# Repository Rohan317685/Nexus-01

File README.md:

<h1 align="center">
  <br>
  </a>
  <br>
  Nexus 01
  <br>
</h1>

<h4 align="center">
A Raspberry Pi Pico-sized devboard!

<div align="center">

</div>

<p align="center">
  <a href="#key-features">Key Features</a> •
  <a href="#pcb">PCB</a> •
  <a href="#credits">Credits</a> •
  <a href="#license">License</a>
</p>

## Key Features

- **Raspberry Pi RP2040 chip** pico like devboard
- **Multiple LED** for visual feedback
- **USB-C**
- **2-layer PCB** designed for cheap prices at bulk
- **Panelized design** for cost-effective manufacturing
- **Multiple buttons** for reset, boot and extra inbuilt button

## PCB

Designed in KiCad with help of the hackclub blueprint guide and a few more features added!

### Schematic

### PCB Layers

The 2-layer stackup:

**Layer 1 (Main routing layer):**

**Layer 2 (Mainly GPIO pins):**

**Front:**

**Back:**

### JLCPCB Order and LCSC Order

| Item | Description | Part Number | LCSC Code | Qty |
| :--- | :--- | :--- | :--- | :--- |
| **Tactile Switch** | SPST SMD 3.9x2.9mm | ALPS SKRKAHE020 | [C202388](https://www.lcsc.com/product-detail/C202388.html?s_z=n_q_C202388) | 10 || **3-Pin Header** | 1x3P 2.54mm Pitch TH | HX PZ2.54-1x3P ZZ | [C32713269](https://www.lcsc.com/product-detail/C32713269.html) | 5 |
| **3-Pin Header** | 1x3P 2.54mm Pitch TH | HX PZ2.54-1x3P ZZ | [C32713269](https://www.lcsc.com/product-detail/C32713269.html?s_z=n_q_C32713269) | 5 |
| **20-Pin Header** | 1x20P 2.54mm Pitch TH | PH2.54-1X20P-H25 | [C42431804](https://www.lcsc.com/product-detail/C42431804.html?s_z=n_q_C42431804) | 5 |

 (Had to get 5 because only multiples of 5 were allowed also got 10 buttons because I want to practice smd hand soldering and I will messup)
 Im buying from LCSC mainly because no companies atleast reliable companies sell those types of exact switches and those headers (I looked at aliexpress, digikey, mouser , rapid electronics and a few more and I decided this has the best price and very good shipping rates!)

### Order costs
- **Parts Total:** $2.25
- **Shipping:** $5.85
- **Handling Fee:** $3.00
- **PCBA:** $39.63
- **PCBA shipping:** $1.50
- **Overall Total:** **$52.23**
## Credits

This project uses:

- [KiCad](https://www.kicad.org/)
- [Onshape](https://www.onshape.com/) for 3D renders
- [Hack Club Macondo go join!!!](https://macondo.hackclub.com/projects/8)

## License

MIT

---

> Readme inspired by [@NotARoomba](https://github.com/NotARoomba) &nbsp;&middot;&nbsp; go follow him now!!! : D

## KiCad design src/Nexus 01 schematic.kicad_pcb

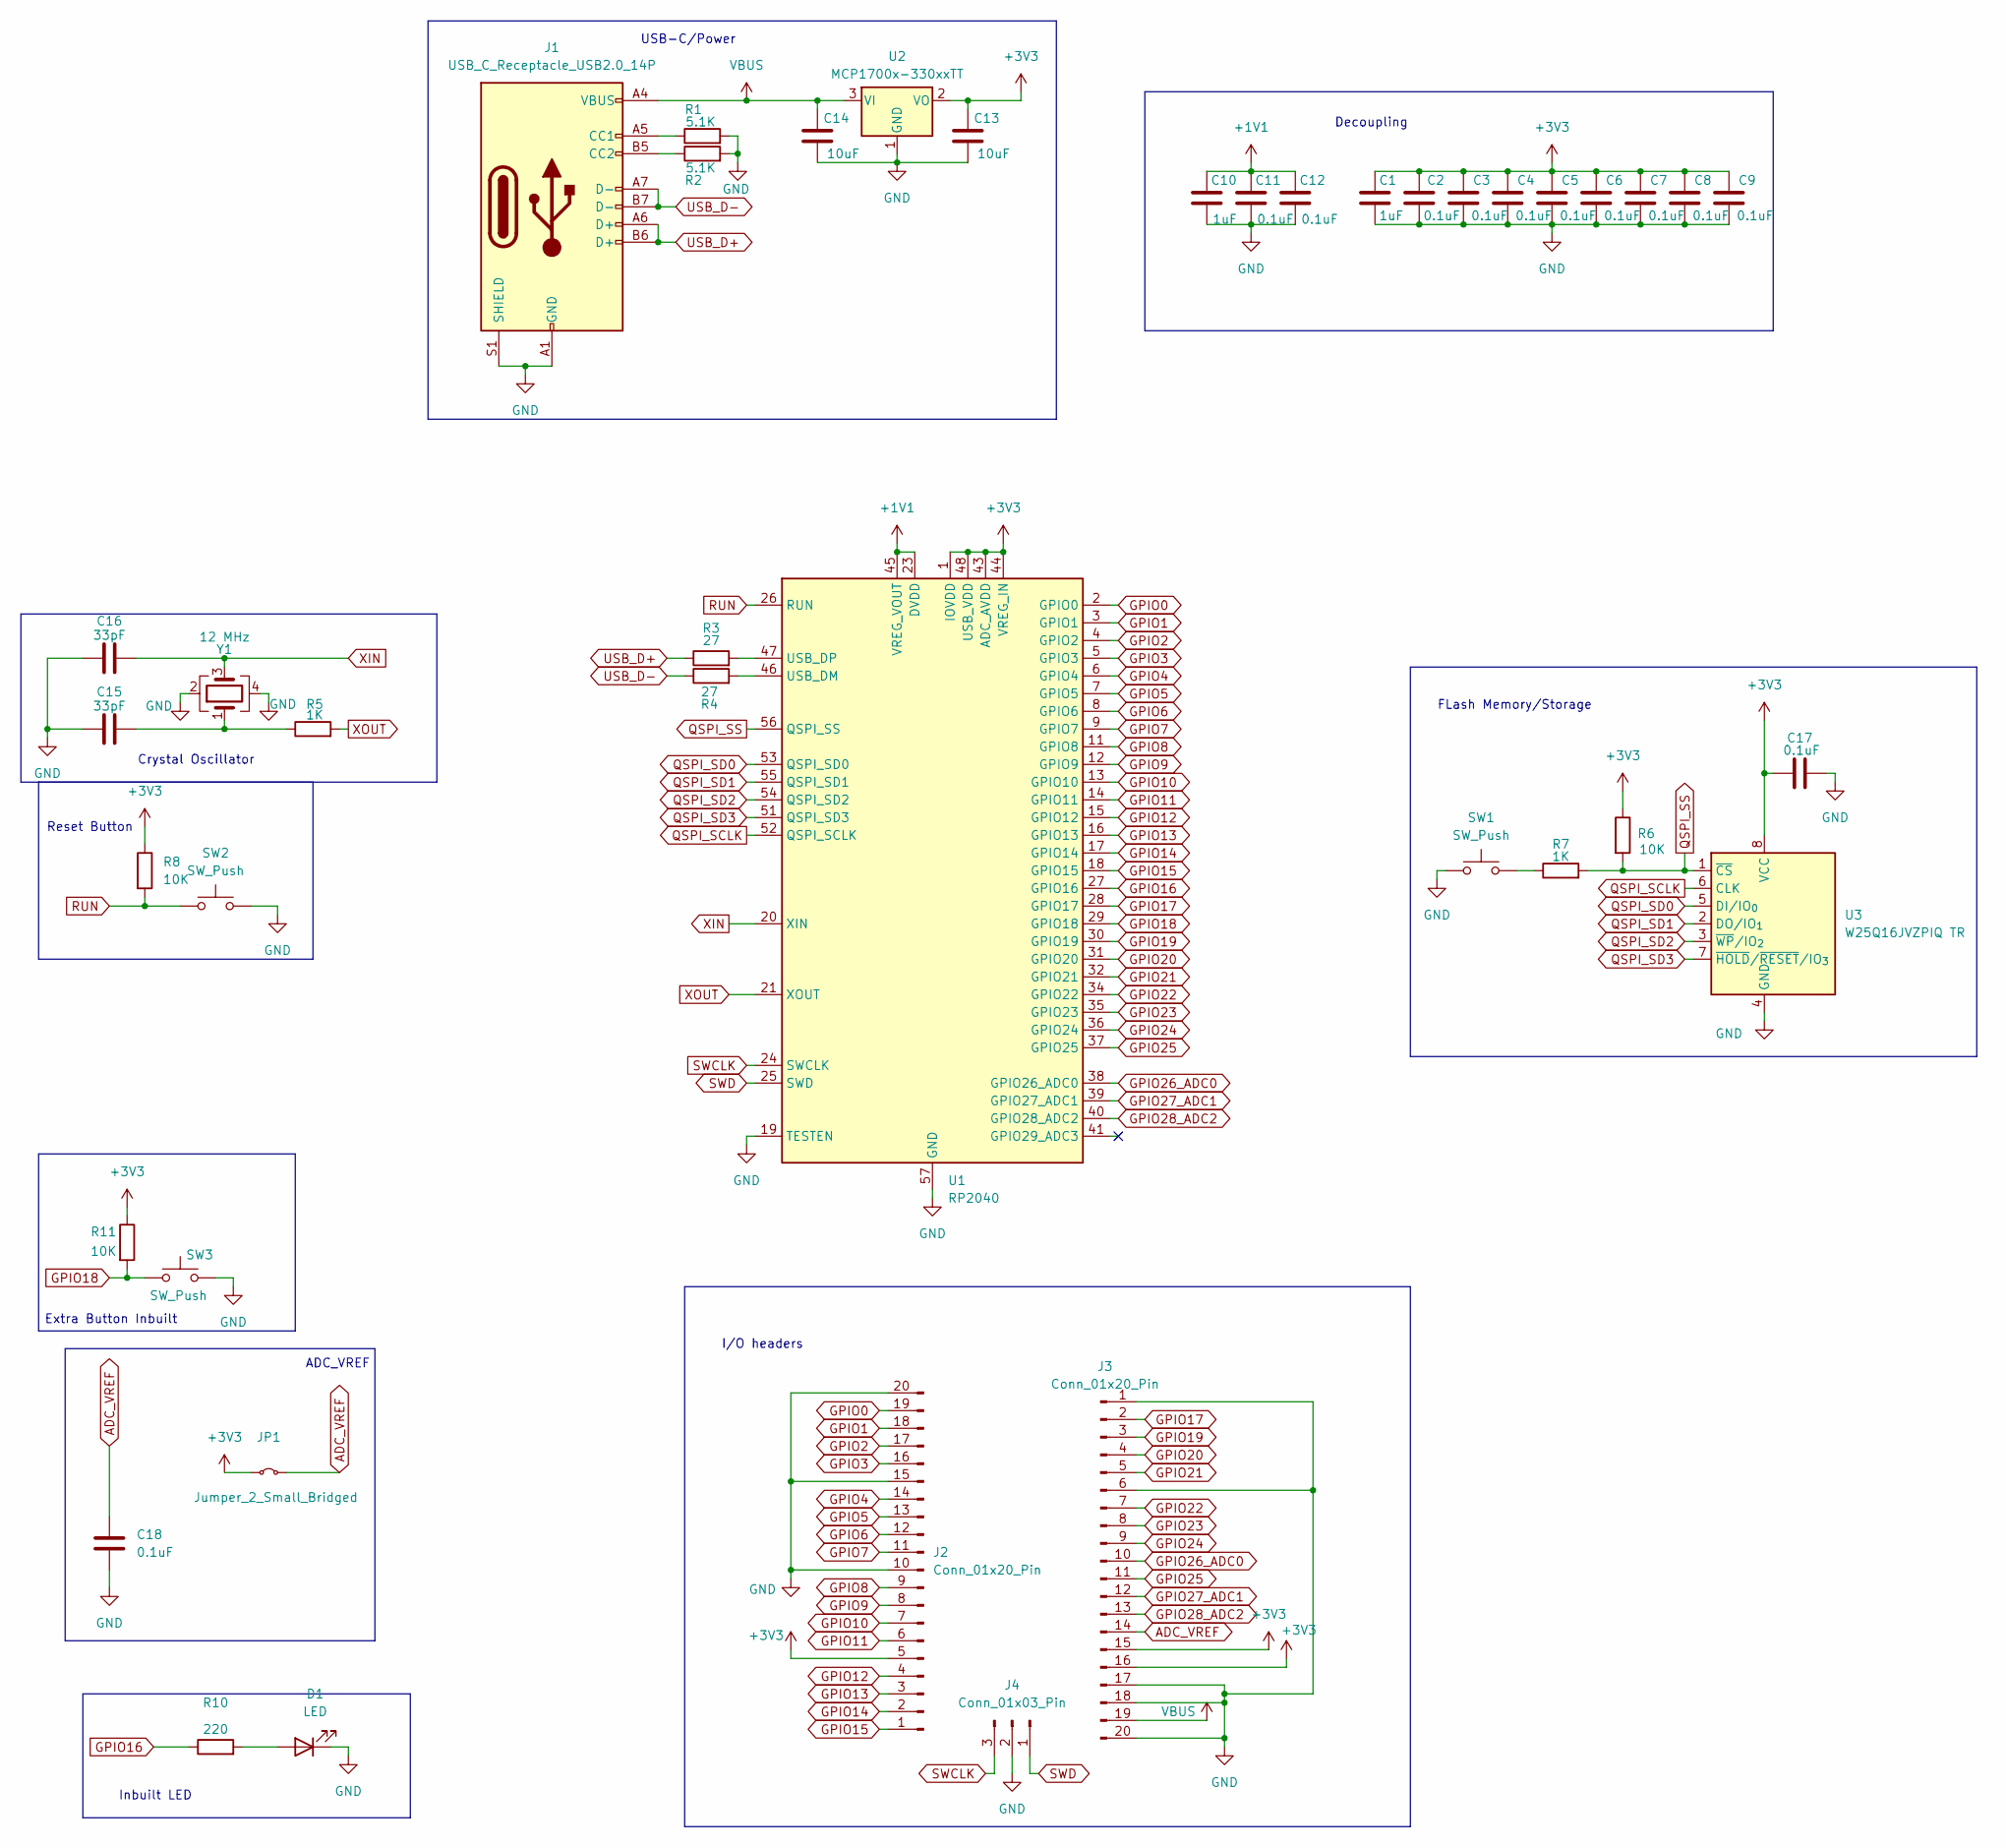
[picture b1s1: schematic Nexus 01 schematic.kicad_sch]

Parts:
C1, C10: 1uF; C_0402_1005Metric
C2, C3, C4, C5, C6, C7, C8, C9, C11, C12, C17, C18: 0.1uF; C_0402_1005Metric
C13, C14: 10uF; C_0402_1005Metric
C15, C16: 33pF; C_0402_1005Metric
D1: LED; LED_0603_1608Metric
J1: USB_C_Receptacle_USB2.0_14P; USB_C_Receptacle_HRO_TYPE-C-31-M-12
J2, J3: Conn_01x20_Pin; PinHeader_1x20_P2.54mm_Vertical
J4: Conn_01x03_Pin; PinHeader_1x03_P2.54mm_Vertical
JP1: Jumper_2_Small_Bridged; SolderJumper-2_P1.3mm_Bridged2Bar_Pad1.0x1.5mm
R1, R2: 5.1K; R_0402_1005Metric
R3, R4: 27; R_0402_1005Metric
R5, R7: 1K; R_0402_1005Metric
R6, R8, R11: 10K; R_0402_1005Metric
R10: 220; R_0402_1005Metric
SW1, SW2, SW3: SW_Push; SW_Push_SPST_NO_Alps_SKRK
U1: RP2040; QFN-56-1EP_7x7mm_P0.4mm_EP3.2x3.2mm
U2: MCP1700x-330xxTT; SOT-23
U3: W25Q16JVZPIQ TR; Winbond_USON-8-1EP_3x2mm_P0.5mm_EP0.2x1.6mm
Y1: 12 MHz; Crystal_SMD_3225-4Pin_3.2x2.5mm

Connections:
+1V1: C10.1, C11.1, C12.1, U1.23 (DVDD), U1.45 (VREG_VOUT), U1.50 (DVDD)
+3V3: C1.1, C2.1, C3.1, C4.1, C5.1, C6.1, C7.1, C8.1, C9.1, C13.1, C17.1, J2.5, J3.15, J3.16, JP1.1 (A), R6.1, R8.1, R11.1, U1.1 (IOVDD), U1.10 (IOVDD), U1.22 (IOVDD), U1.33 (IOVDD), U1.42 (IOVDD), U1.43 (ADC_AVDD), U1.44 (VREG_IN), U1.48 (USB_VDD), U1.49 (IOVDD), U2.2 (VO), U3.8 (VCC)
ADC_VREF: C18.1, J3.14, JP1.2 (B)
GND: C1.2, C2.2, C3.2, C4.2, C5.2, C6.2, C7.2, C8.2, C9.2, C10.2, C11.2, C12.2, C13.2, C14.2, C15.1, C16.1, C17.2, C18.2, D1.1 (K), J1.A1 (GND), J1.A12 (GND), J1.B1 (GND), J1.B12 (GND), J1.S1 (SHIELD), J2.10, J2.15, J2.20, J3.1, J3.6, J3.17, J3.18, J3.20, J4.2, R1.2, R2.2, SW1.1, SW2.2, SW3.2, U1.19 (TESTEN), U1.57 (GND), U2.1 (GND), U3.4 (GND), Y1.2, Y1.4
GPIO0: J2.19, U1.2 (GPIO0)
GPIO1: J2.18, U1.3 (GPIO1)
GPIO2: J2.17, U1.4 (GPIO2)
GPIO3: J2.16, U1.5 (GPIO3)
GPIO4: J2.14, U1.6 (GPIO4)
GPIO5: J2.13, U1.7 (GPIO5)
GPIO6: J2.12, U1.8 (GPIO6)
GPIO7: J2.11, U1.9 (GPIO7)
GPIO8: J2.9, U1.11 (GPIO8)
GPIO9: J2.8, U1.12 (GPIO9)
GPIO10: J2.7, U1.13 (GPIO10)
GPIO11: J2.6, U1.14 (GPIO11)
GPIO12: J2.4, U1.15 (GPIO12)
GPIO13: J2.3, U1.16 (GPIO13)
GPIO14: J2.2, U1.17 (GPIO14)
GPIO15: J2.1, U1.18 (GPIO15)
GPIO16: R10.1, U1.27 (GPIO16)
GPIO17: J3.2, U1.28 (GPIO17)
GPIO18: R11.2, SW3.1, U1.29 (GPIO18)
GPIO19: J3.3, U1.30 (GPIO19)
GPIO20: J3.4, U1.31 (GPIO20)
GPIO21: J3.5, U1.32 (GPIO21)
GPIO22: J3.7, U1.34 (GPIO22)
GPIO23: J3.8, U1.35 (GPIO23)
GPIO24: J3.9, U1.36 (GPIO24)
GPIO25: J3.11, U1.37 (GPIO25)
GPIO26_ADC0: J3.10, U1.38 (GPIO26_ADC0)
GPIO27_ADC1: J3.12, U1.39 (GPIO27_ADC1)
GPIO28_ADC2: J3.13, U1.40 (GPIO28_ADC2)
unnamed: C15.2, R5.1, Y1.1
unnamed: D1.2 (A), R10.2
unnamed: J1.A5 (CC1), R1.1
unnamed: J1.B5 (CC2), R2.1
unnamed: R7.1, SW1.2
unnamed: R4.2, U1.46 (USB_DM)
unnamed: R3.2, U1.47 (USB_DP)
QSPI_SCLK: U1.52 (QSPI_SCLK), U3.6 (CLK)
QSPI_SD0: U1.53 (QSPI_SD0), U3.5 (DI/IO_{0})
QSPI_SD1: U1.55 (QSPI_SD1), U3.2 (DO/IO_{1})
QSPI_SD2: U1.54 (QSPI_SD2), U3.3 (~WP/IO_{2})
QSPI_SD3: U1.51 (QSPI_SD3), U3.7 (~HOLD/~RESET/IO_{3})
QSPI_SS: R6.2, R7.2, U1.56 (QSPI_SS), U3.1 (~CS)
RUN: R8.2, SW2.1, U1.26 (RUN)
SWCLK: J4.3, U1.24 (SWCLK)
SWD: J4.1, U1.25 (SWD)
USB_D+: J1.A6 (D+), J1.B6 (D+), R3.1
USB_D-: J1.A7 (D-), J1.B7 (D-), R4.1
VBUS: C14.1, J1.A4 (VBUS), J1.A9 (VBUS), J1.B4 (VBUS), J1.B9 (VBUS), J3.19, U2.3 (VI)
XIN: C16.2, U1.20 (XIN), Y1.3
XOUT: R5.2, U1.21 (XOUT)

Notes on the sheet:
Crystal Oscillator
Inbuilt LED
Decoupling
Extra Button Inbuilt
ADC_VREF
I/O headers
FLash Memory/Storage
USB-C/Power
Reset Button

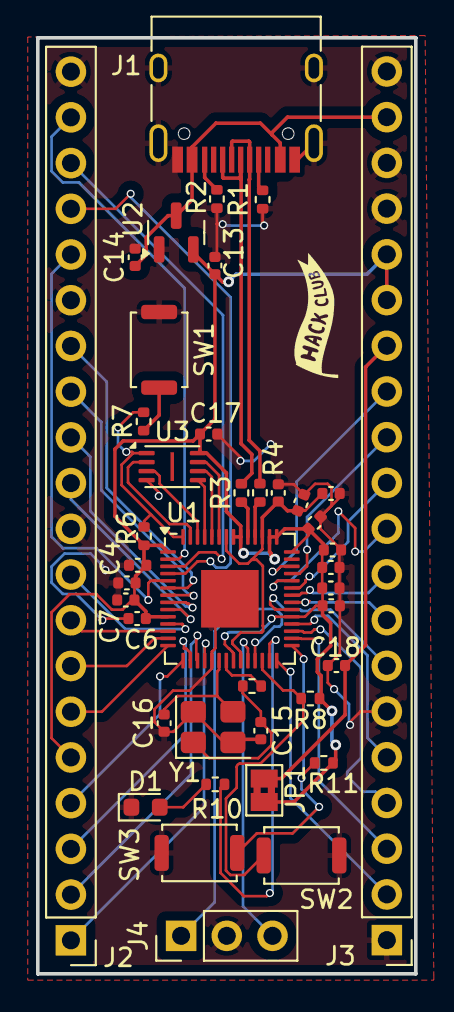
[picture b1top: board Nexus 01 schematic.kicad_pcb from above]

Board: 2 copper layers, 21.0 x 52.0 mm, 41 parts (0 on the bottom side), 54 nets.

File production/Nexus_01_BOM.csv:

Designator,Footprint,Quantity,Comment,LCSC Part #,,
"C1, C10",402,2,1uF,,,C52923
"C11, C12, C17, C18, C2, C3, C4, C5, C6, C7, C8, C9",402,12,0.1uF,,,C1525
"C13, C14",402,2,10uF,,,C15525
"C15, C16",402,2,33pF,,,C1562
D1,603,1,LED,,,C2290
J1,USB_C_Receptacle_HRO_TYPE-C-31-M-12,1,USB_C_Receptacle_USB2.0_14P,,,C165948
"J2, J3",PinHeader_1x20_P2.54mm_Vertical,2,Conn_01x20_Pin,,,
J4,PinHeader_1x03_P2.54mm_Vertical,1,Conn_01x03_Pin,,,
JP1,SolderJumper-2_P1.3mm_Bridged2Bar_Pad1.0x1.5mm,1,Jumper_2_Small_Bridged,,,
"R1, R2",402,2,5.1K,,,C25905
R10,402,1,220,,,C25091
"R11, R6, R8",402,3,10K,,,C25744
"R3, R4",402,2,27,,,C25100
"R5, R7",402,2,1K,,,C11702
"SW1, SW2, SW3",SW_Push_SPST_NO_Alps_SKRK,3,SW_Push,,,C115357
U1,QFN-56-1EP_7x7mm_P0.4mm_EP3.2x3.2mm,1,RP2040,,,C2040
U2,SOT-23,1,MCP1700x-330xxTT,,,C2132
U3,Winbond_USON-8-1EP_3x2mm_P0.5mm_EP0.2x1.6mm,1,W25Q16JVZPIQ TR,,,C2456208
Y1,Crystal_SMD_3225-4Pin_3.2x2.5mm,1,12 MHz,,,C481407

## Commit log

2026-04-29 rebrand nathans stolen repo
2026-04-29 typo fixed
2026-04-29 Revise README content and update banner image
    Updated the README to simplify the description and change the banner image.
2026-04-29 Update overall total and add PCBA costs
2026-05-03 Fix LCSC link for 3-Pin Header in README
    Updated LCSC link for 3-Pin Header in the table.
